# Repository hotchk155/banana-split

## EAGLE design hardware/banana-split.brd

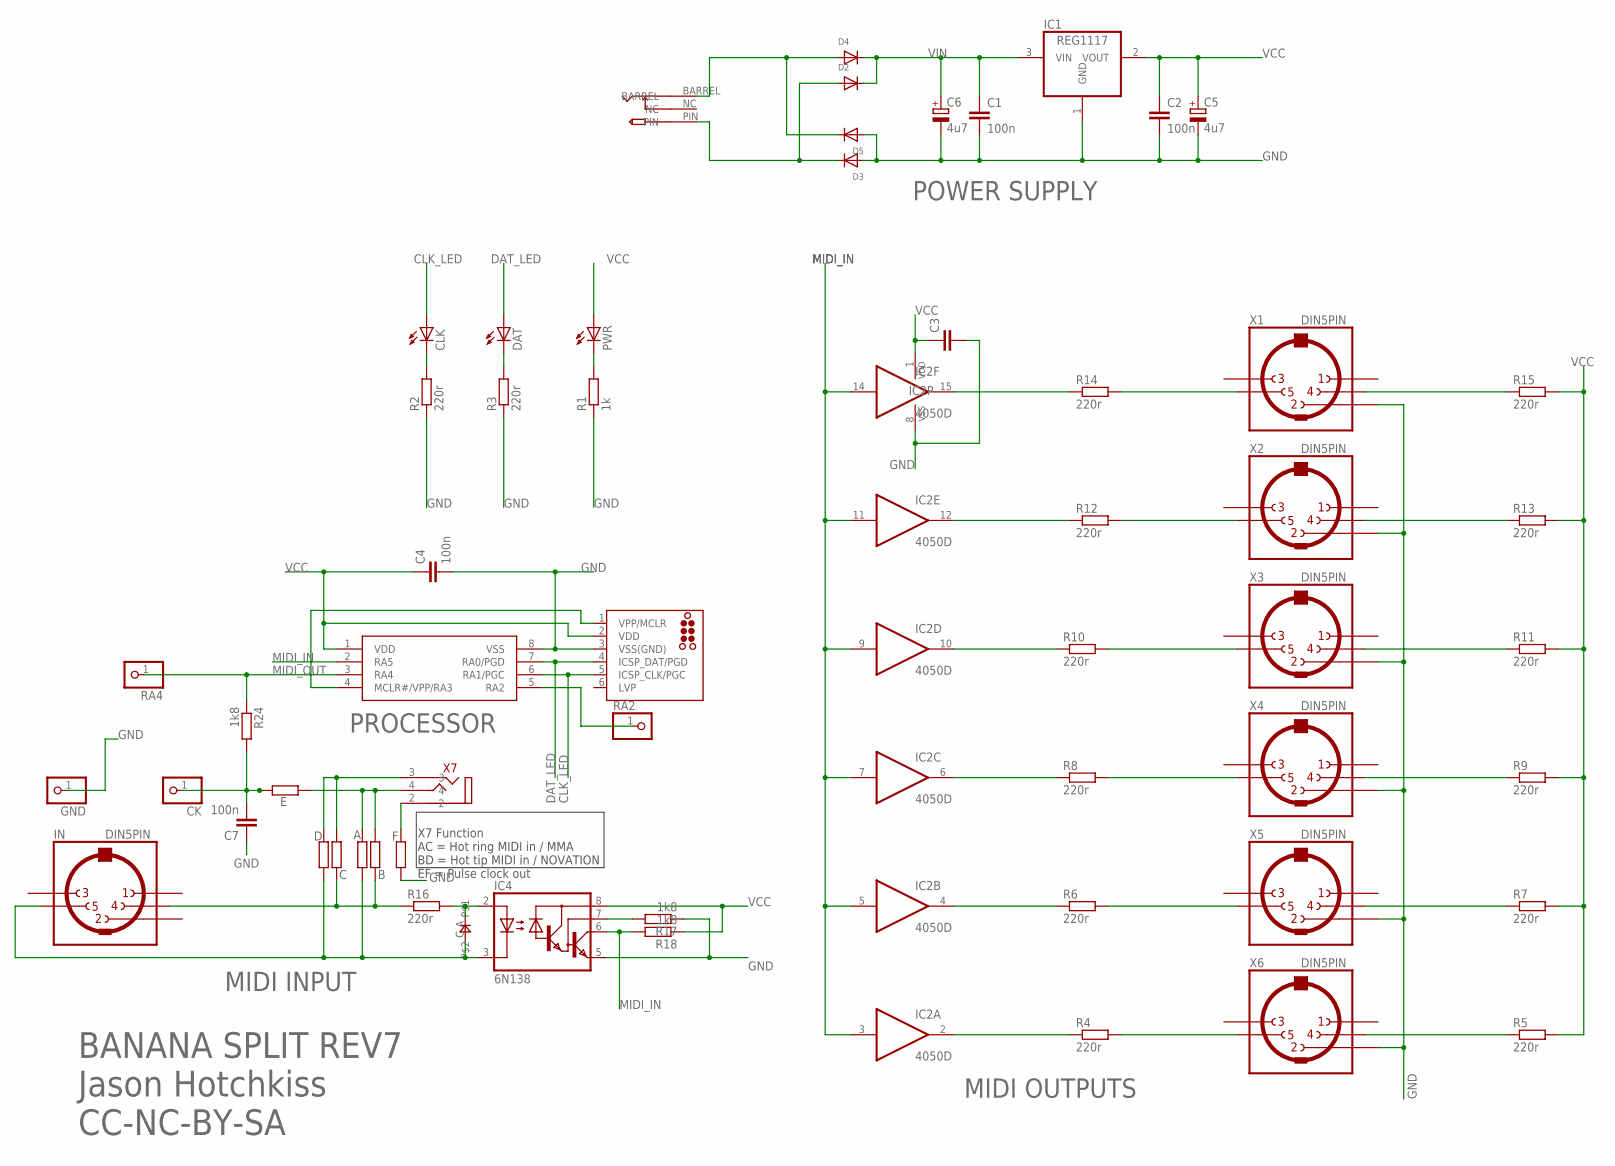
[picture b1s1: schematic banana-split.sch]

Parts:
A: 1k8; R0805
B: 1k8; R0805
C: 1k8; R0805
C1, C2, C4, C7: 100n; C0805
C3: C-EUC0805; C0805
C5, C6: 4u7; E2-4
CK: PINHD-1X1; 1X01
CLK: LED3MM
D: 1k8; R0805
D1: 0805DIODE
D2, D3, D4, D5: DIODESOD-123; SOD-123
DAT: LED3MM
E: 1k8; R0805
F: 1k8; R0805
GND: PINHD-1X1; 1X01
IC1: REG1117; SOT223
IC2: 4050D; SO16
IC3: PIC12F1822SO08; SO08
IC4: 6N138; DIL08
ICSP: TC2030-MCP-NL
IN: DIN5PIN; EDGEDIN
PWR: LED3MM
R1: 1k; R0805
R2, R3, R4, R5, R6, R7, R8, R9, R10, R11, R12, R13, R14, R15, R16: 220r; R0805
R17, R18, R24: 1k8; R0805
RA2, RA4: PINHD-1X1; 1X01
U$1: PWR_SOCKET_2_1MM
X1, X2, X3, X4, X5, X6: DIN5PIN; EDGEDIN
X7: VERTICAL_3_5MM_SOCKET

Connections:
CLK: CLK.K (C), R2.2
CLK_LED: CLK.A, IC3.6 (RA1/PGC), ICSP.5 (ICSP_CLK/PGC)
DAT_LED: DAT.A, IC3.7 (RA0/PGD), ICSP.4 (ICSP_DAT/PGD)
GND: C1.2, C2.2, C3.2, C4.2, C5.-, C6.-, C7.1, D3.A, D5.A, F.1, GND.1, IC1.1 (GND), IC2.8 (VSS), IC3.8 (VSS), IC4.5 (GND), ICSP.3 (VSS(GND)), R1.1, R2.1, R3.1, R17.1, X1.2, X2.2, X3.2, X4.2, X5.2, X6.2
MIDI_IN: IC2.3 (I), IC2.5 (I), IC2.7 (I), IC2.9 (I), IC2.11 (I), IC2.14 (I), IC3.2 (RA5), IC4.6 (VO), R18.2
MIDI_OUT: IC3.3 (RA4), R24.1, RA4.1
unnamed: R14.2, X1.5
unnamed: R12.2, X2.5
unnamed: R10.2, X3.5
unnamed: R8.2, X4.5
unnamed: R6.2, X5.5
unnamed: R4.2, X6.5
unnamed: IC2.15 (O), R14.1
unnamed: IC2.12 (O), R12.1
unnamed: IC2.10 (O), R10.1
unnamed: IC2.6 (O), R8.1
unnamed: IC2.2 (O), R4.1
unnamed: IC2.4 (O), R6.1
unnamed: PWR.K (C), R1.2
unnamed: R15.1, X1.4
unnamed: R13.1, X2.4
unnamed: R11.1, X3.4
unnamed: R9.1, X4.4
unnamed: R7.1, X5.4
unnamed: R5.1, X6.4
unnamed: B.1, C.1, IN.4, R16.1
unnamed: D1.A, IC4.2 (A), R16.2
unnamed: IC4.7 (VB), R17.2
unnamed: DAT.K (C), R3.2
unnamed: A.1, D.1, D1.C, IC4.3 (C), IN.5
unnamed: IC3.5 (RA2), RA2.1
unnamed: C.2, D.2, X7.3
unnamed: D4.A, D5.C, U$1.BARREL
unnamed: D2.A, D3.C, U$1.PIN
unnamed: F.2, X7.2
unnamed: A.2, B.2, E.2, X7.4
unnamed: C7.2, CK.1, E.1, R24.2
unnamed: IC3.4 (MCLR#/VPP/RA3), ICSP.1 (VPP/MCLR)
VCC: C2.1, C3.1, C4.1, C5.+, IC1.2 (VOUT), IC2.1 (VDD), IC3.1 (VDD), IC4.8 (VCC), ICSP.2 (VDD), PWR.A, R5.2, R7.2, R9.2, R11.2, R13.2, R15.2, R18.1
VIN: C1.1, C6.+, D2.C, D4.C, IC1.3 (VIN)

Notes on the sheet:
POWER SUPPLY
MIDI OUTPUTS
MIDI INPUT
PROCESSOR
BANANA SPLIT REV7
Jason Hotchkiss CC-NC-BY-SA
X7 Function AC = Hot ring MIDI in / MMA BD = Hot tip MIDI in / NOVATION EF = Pulse clock out

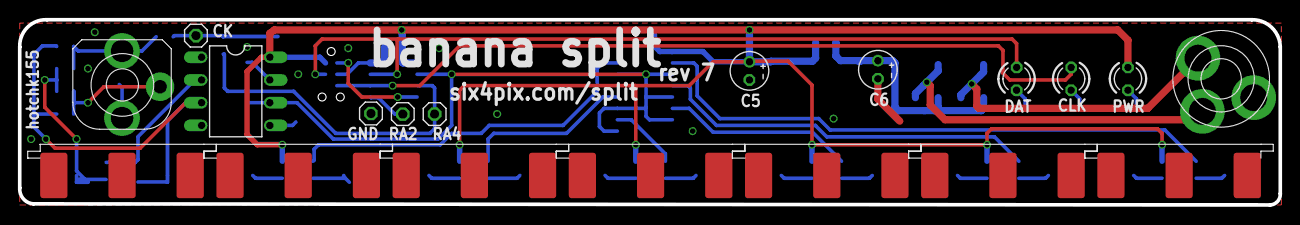
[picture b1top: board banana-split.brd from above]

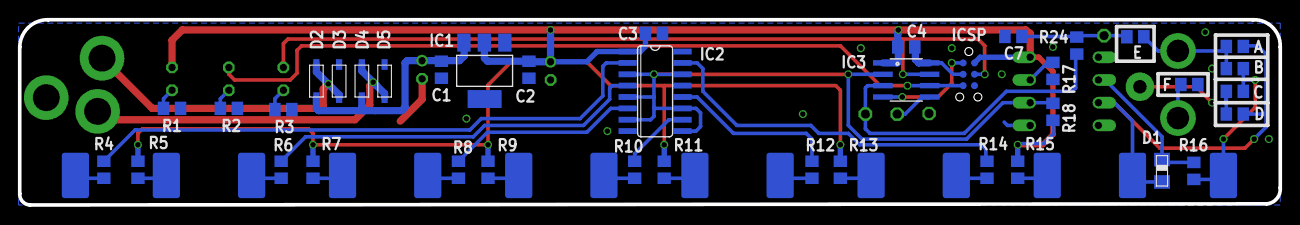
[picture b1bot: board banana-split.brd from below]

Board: 2 copper layers, 140.8 x 20.7 mm, 58 parts (39 on the bottom side), 40 nets.

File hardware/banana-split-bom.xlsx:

Comment | Designator | Footprint | JLCPCB Part #（optional）
0r | A | 0805
DNP | B
0r | C | 0805
100nF | C1 | 0805
100nF | C2 | 0805
100nF | C3 | 0805
100nF | C4 | 0805
100nF | C7 | 0805
DNP | D
TS4148 | D1 | 0805
MBR0520 | D2 | SOD-123
MBR0520 | D3 | SOD-123
MBR0520 | D4 | SOD-123
MBR0520 | D5 | SOD-123
DNP | E
DNP | F
LD1117S50CTR | IC1 | SOT223
CD4050BD | IC2 | SO16
PIC12F1822-I/P | IC3 | SO08
1k | R1 | 0805
220r | R2 | 0805
220r | R3 | 0805
220r | R4 | 0805
220r | R5 | 0805
220r | R6 | 0805
220r | R7 | 0805
220r | R8 | 0805
220r | R9 | 0805
220r | R10 | 0805
220r | R11 | 0805
220r | R12 | 0805
220r | R13 | 0805
220r | R14 | 0805
220r | R15 | 0805
220r | R16 | 0805
1k5 | R17 | 0805
1k5 | R18 | 0805
1k | R24 | 0805

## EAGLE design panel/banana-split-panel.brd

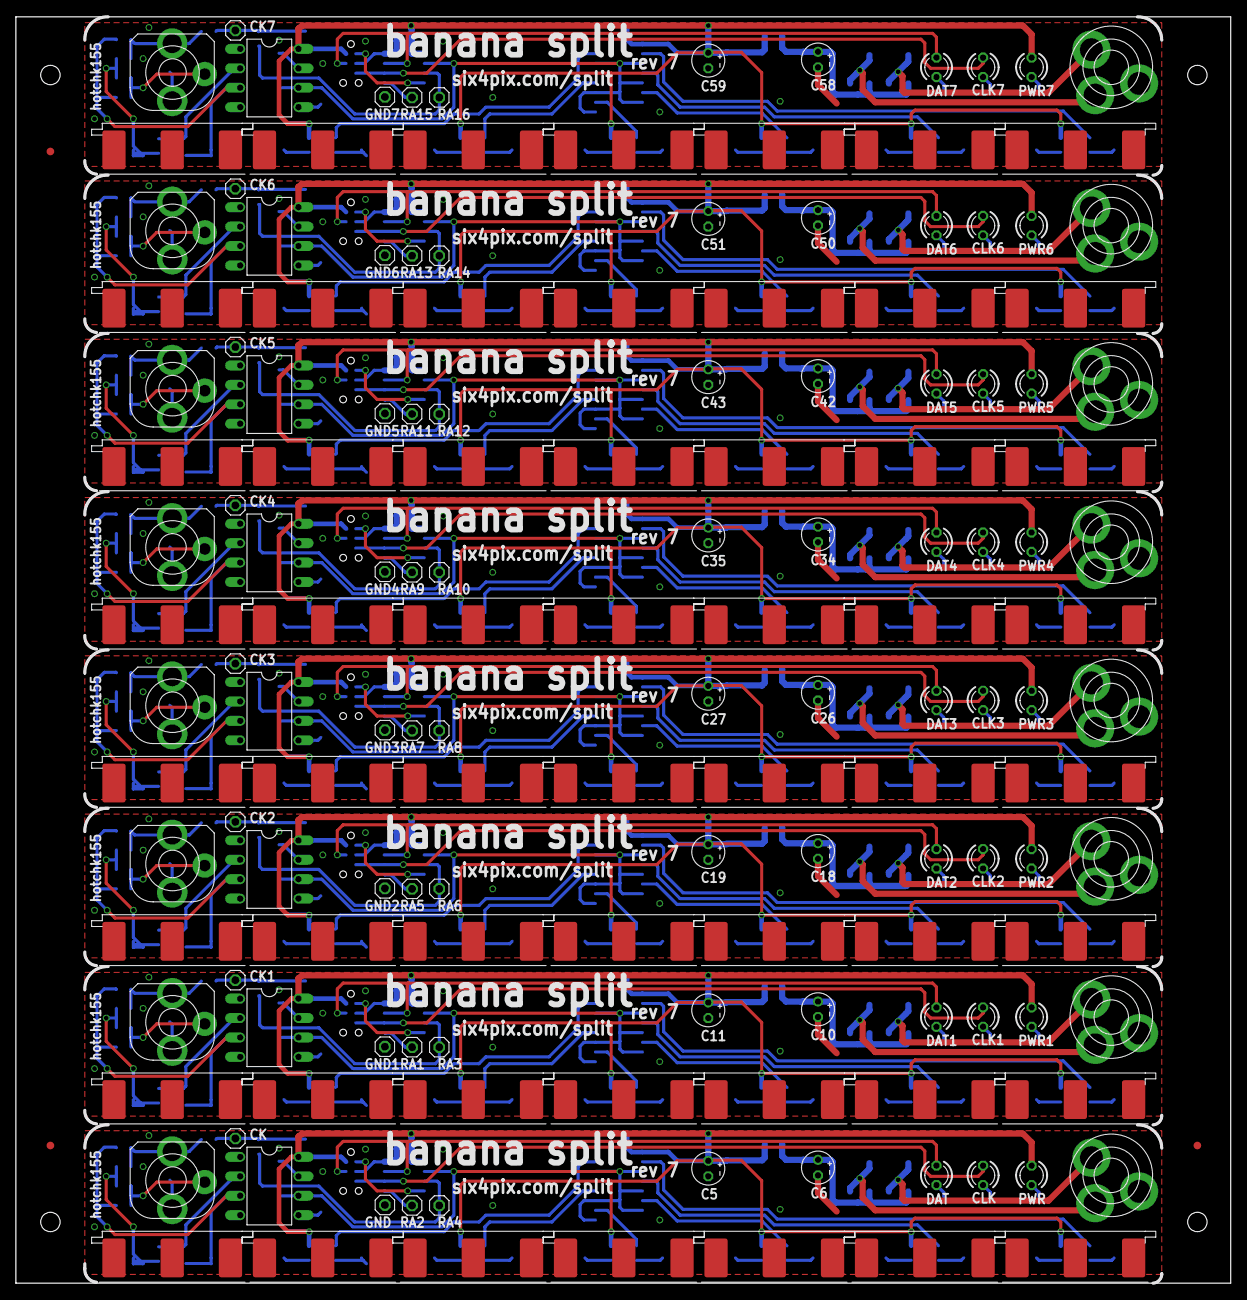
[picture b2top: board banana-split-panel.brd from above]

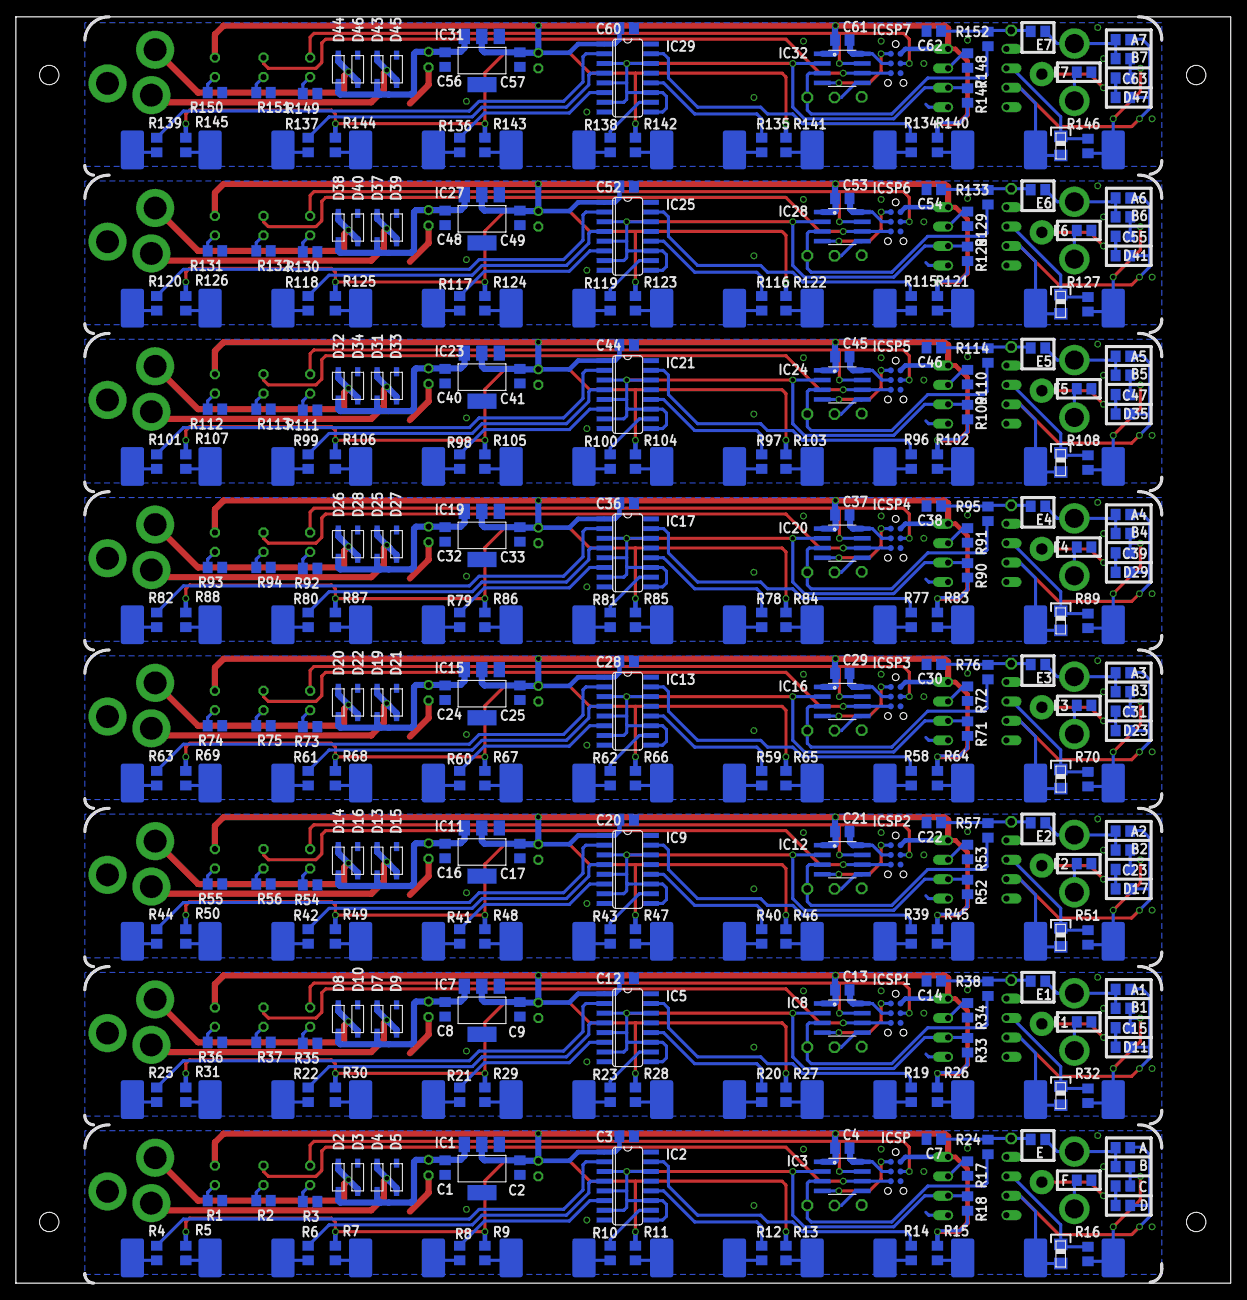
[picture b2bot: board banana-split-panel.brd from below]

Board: 2 copper layers, 158.9 x 165.6 mm, 467 parts (312 on the bottom side), 320 nets.

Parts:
A, A1, A2, A3, A4, A5, A6, A7: 1k8; R0805
B, B1, B2, B3, B4, B5, B6, B7: 1k8; R0805
C, C15, C23, C31, C39, C47, C55, C63: 1k8; R0805
C1, C2, C4, C7, C8, C9, C13, C14, C16, C17, C21, C22, C24, C25, C29, C30, C32, C33, C37, C38, C40, C41, C45, C46, C48, C49, C53, C54, C56, C57, C61, C62: 100n; C0805
C3, C12, C20, C28, C36, C44, C52, C60: C0805
C5, C6, C10, C11, C18, C19, C26, C27, C34, C35, C42, C43, C50, C51, C58, C59: 4u7; E2-4
CK, CK1, CK2, CK3, CK4, CK5, CK6, CK7: 1X01
CLK, CLK1, CLK2, CLK3, CLK4, CLK5, CLK6, CLK7: LED3MM
D, D11, D17, D23, D29, D35, D41, D47: 1k8; R0805
D1, D6, D12, D18, D24, D30, D36, D42: 0805DIODE
D2, D3, D4, D5, D7, D8, D9, D10, D13, D14, D15, D16, D19, D20, D21, D22, D25, D26, D27, D28, D31, D32, D33, D34, D37, D38, D39, D40, D43, D44, D45, D46: SOD-123
DAT, DAT1, DAT2, DAT3, DAT4, DAT5, DAT6, DAT7: LED3MM
E, E1, E2, E3, E4, E5, E6, E7: 1k8; R0805
E$1, E$2, E$3: FIDUCIAL_1MM
F, F1, F2, F3, F4, F5, F6, F7: 1k8; R0805
GND, GND1, GND2, GND3, GND4, GND5, GND6, GND7: 1X01
IC1, IC7, IC11, IC15, IC19, IC23, IC27, IC31: REG1117; SOT223
IC2, IC5, IC9, IC13, IC17, IC21, IC25, IC29: 4050D; SO16
IC3, IC8, IC12, IC16, IC20, IC24, IC28, IC32: PIC12F1822SO08; SO08
IC4, IC6, IC10, IC14, IC18, IC22, IC26, IC30: 6N138; DIL08
ICSP, ICSP1, ICSP2, ICSP3, ICSP4, ICSP5, ICSP6, ICSP7: TC2030-MCP-NL
IN, IN1, IN2, IN3, IN4, IN5, IN6, IN7: DIN5PIN; EDGEDIN
PWR, PWR1, PWR2, PWR3, PWR4, PWR5, PWR6, PWR7: LED3MM
R1, R36, R55, R74, R93, R112, R131, R150: 1k; R0805
R2, R3, R4, R5, R6, R7, R8, R9, R10, R11, R12, R13, R14, R15, R16, R19, R20, R21, R22, R23, R25, R26, R27, R28, R29, R30, R31, R32, R35, R37, R39, R40, R41, R42, R43, R44, R45, R46, R47, R48, R49, R50, R51, R54, R56, R58, R59, R60, R61, R62, R63, R64, R65, R66, R67, R68, R69, R70, R73, R75, R77, R78, R79, R80, R81, R82, R83, R84, R85, R86, R87, R88, R89, R92, R94, R96, R97, R98, R99, R100, R101, R102, R103, R104, R105, R106, R107, R108, R111, R113, R115, R116, R117, R118, R119, R120, R121, R122, R123, R124, R125, R126, R127, R130, R132, R134, R135, R136, R137, R138, R139, R140, R141, R142, R143, R144, R145, R146, R149, R151: 220r; R0805
R17, R18, R24, R33, R34, R38, R52, R53, R57, R71, R72, R76, R90, R91, R95, R109, R110, R114, R128, R129, R133, R147, R148, R152: 1k8; R0805
RA1, RA2, RA3, RA4, RA5, RA6, RA7, RA8, RA9, RA10, RA11, RA12, RA13, RA14, RA15, RA16: 1X01
U$1, U$2, U$3, U$4, U$5, U$6, U$7, U$8: PWR_SOCKET_2_1MM
X1, X2, X3, X4, X5, X6, X8, X9, X10, X11, X12, X13, X15, X16, X17, X18, X19, X20, X22, X23, X24, X25, X26, X27, X29, X30, X31, X32, X33, X34, X36, X37, X38, X39, X40, X41, X43, X44, X45, X46, X47, X48, X50, X51, X52, X53, X54, X55: DIN5PIN; EDGEDIN
X7, X14, X21, X28, X35, X42, X49, X56: VERTICAL_3_5MM_SOCKET

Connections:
CLK: CLK.K, R2.2
CLK1: CLK1.K, R37.2
CLK2: CLK2.K, R56.2
CLK3: CLK3.K, R75.2
CLK4: CLK4.K, R94.2
CLK5: CLK5.K, R113.2
CLK6: CLK6.K, R132.2
CLK7: CLK7.K, R151.2
CLK_LED: CLK.A, IC3.6, ICSP.5
CLK_LED1: CLK1.A, IC8.6, ICSP1.5
CLK_LED2: CLK2.A, IC12.6, ICSP2.5
CLK_LED3: CLK3.A, IC16.6, ICSP3.5
CLK_LED4: CLK4.A, IC20.6, ICSP4.5
CLK_LED5: CLK5.A, IC24.6, ICSP5.5
CLK_LED6: CLK6.A, IC28.6, ICSP6.5
CLK_LED7: CLK7.A, IC32.6, ICSP7.5
DAT_LED: DAT.A, IC3.7, ICSP.4
DAT_LED1: DAT1.A, IC8.7, ICSP1.4
DAT_LED2: DAT2.A, IC12.7, ICSP2.4
DAT_LED3: DAT3.A, IC16.7, ICSP3.4
DAT_LED4: DAT4.A, IC20.7, ICSP4.4
DAT_LED5: DAT5.A, IC24.7, ICSP5.4
DAT_LED6: DAT6.A, IC28.7, ICSP6.4
DAT_LED7: DAT7.A, IC32.7, ICSP7.4
GND: C1.2, C2.2, C3.2, C4.2, C5.-, C6.-, C7.1, D3.A, D5.A, F.1, GND.1, IC1.1, IC2.8, IC3.8, IC4.5, ICSP.3, R1.1, R2.1, R3.1, R17.1, X1.2, X2.2, X3.2, X4.2, X5.2, X6.2
GND1: C8.2, C9.2, C10.-, C11.-, C12.2, C13.2, C14.1, D9.A, D10.A, F1.1, GND1.1, IC5.8, IC6.5, IC7.1, IC8.8, ICSP1.3, R34.1, R35.1, R36.1, R37.1, X8.2, X9.2, X10.2, X11.2, X12.2, X13.2
GND2: C16.2, C17.2, C18.-, C19.-, C20.2, C21.2, C22.1, D15.A, D16.A, F2.1, GND2.1, IC9.8, IC10.5, IC11.1, IC12.8, ICSP2.3, R53.1, R54.1, R55.1, R56.1, X15.2, X16.2, X17.2, X18.2, X19.2, X20.2
GND3: C24.2, C25.2, C26.-, C27.-, C28.2, C29.2, C30.1, D21.A, D22.A, F3.1, GND3.1, IC13.8, IC14.5, IC15.1, IC16.8, ICSP3.3, R72.1, R73.1, R74.1, R75.1, X22.2, X23.2, X24.2, X25.2, X26.2, X27.2
GND4: C32.2, C33.2, C34.-, C35.-, C36.2, C37.2, C38.1, D27.A, D28.A, F4.1, GND4.1, IC17.8, IC18.5, IC19.1, IC20.8, ICSP4.3, R91.1, R92.1, R93.1, R94.1, X29.2, X30.2, X31.2, X32.2, X33.2, X34.2
GND5: C40.2, C41.2, C42.-, C43.-, C44.2, C45.2, C46.1, D33.A, D34.A, F5.1, GND5.1, IC21.8, IC22.5, IC23.1, IC24.8, ICSP5.3, R110.1, R111.1, R112.1, R113.1, X36.2, X37.2, X38.2, X39.2, X40.2, X41.2
GND6: C48.2, C49.2, C50.-, C51.-, C52.2, C53.2, C54.1, D39.A, D40.A, F6.1, GND6.1, IC25.8, IC26.5, IC27.1, IC28.8, ICSP6.3, R129.1, R130.1, R131.1, R132.1, X43.2, X44.2, X45.2, X46.2, X47.2, X48.2
GND7: C56.2, C57.2, C58.-, C59.-, C60.2, C61.2, C62.1, D45.A, D46.A, F7.1, GND7.1, IC29.8, IC30.5, IC31.1, IC32.8, ICSP7.3, R148.1, R149.1, R150.1, R151.1, X50.2, X51.2, X52.2, X53.2, X54.2, X55.2
MIDI_IN: IC2.3, IC2.5, IC2.7, IC2.9, IC2.11, IC2.14, IC3.2, IC4.6, R18.2
MIDI_IN1: IC5.3, IC5.5, IC5.7, IC5.9, IC5.11, IC5.14, IC6.6, IC8.2, R33.2
MIDI_IN2: IC9.3, IC9.5, IC9.7, IC9.9, IC9.11, IC9.14, IC10.6, IC12.2, R52.2
MIDI_IN3: IC13.3, IC13.5, IC13.7, IC13.9, IC13.11, IC13.14, IC14.6, IC16.2, R71.2
MIDI_IN4: IC17.3, IC17.5, IC17.7, IC17.9, IC17.11, IC17.14, IC18.6, IC20.2, R90.2
MIDI_IN5: IC21.3, IC21.5, IC21.7, IC21.9, IC21.11, IC21.14, IC22.6, IC24.2, R109.2
MIDI_IN6: IC25.3, IC25.5, IC25.7, IC25.9, IC25.11, IC25.14, IC26.6, IC28.2, R128.2
MIDI_IN7: IC29.3, IC29.5, IC29.7, IC29.9, IC29.11, IC29.14, IC30.6, IC32.2, R147.2
MIDI_OUT: IC3.3, R24.1, RA4.1
MIDI_OUT1: IC8.3, R38.1, RA3.1
MIDI_OUT2: IC12.3, R57.1, RA6.1
MIDI_OUT3: IC16.3, R76.1, RA8.1
MIDI_OUT4: IC20.3, R95.1, RA10.1
MIDI_OUT5: IC24.3, R114.1, RA12.1
MIDI_OUT6: IC28.3, R133.1, RA14.1
MIDI_OUT7: IC32.3, R152.1, RA16.1
unnamed: R14.2, X1.5
unnamed: R12.2, X2.5
unnamed: R10.2, X3.5
unnamed: R8.2, X4.5
unnamed: R6.2, X5.5
unnamed: R4.2, X6.5
unnamed: IC2.15, R14.1
unnamed: IC2.12, R12.1
unnamed: IC2.10, R10.1
unnamed: IC2.6, R8.1
unnamed: IC2.2, R4.1
unnamed: IC2.4, R6.1
unnamed: PWR.K, R1.2
unnamed: R15.1, X1.4
unnamed: R13.1, X2.4
unnamed: R11.1, X3.4
unnamed: R9.1, X4.4
unnamed: R7.1, X5.4
unnamed: R5.1, X6.4
unnamed: B.1, C.1, IN.4, R16.1
unnamed: D1.A, IC4.2, R16.2
unnamed: IC4.7, R17.2
unnamed: DAT.K, R3.2
unnamed: A.1, D.1, D1.C, IC4.3, IN.5
unnamed: IC3.5, RA2.1
unnamed: C.2, D.2, X7.3
unnamed: D4.A, D5.C, U$1.BARREL
unnamed: D2.A, D3.C, U$1.PIN
unnamed: F.2, X7.2
unnamed: A.2, B.2, E.2, X7.4
unnamed: C7.2, CK.1, E.1, R24.2
unnamed: R19.2, X8.5
unnamed: IC3.4, ICSP.1
unnamed: R20.2, X9.5
unnamed: R23.2, X10.5
unnamed: R21.2, X11.5
unnamed: R22.2, X12.5
unnamed: R25.2, X13.5
unnamed: R26.1, X8.4
unnamed: R27.1, X9.4
unnamed: R28.1, X10.4
unnamed: R29.1, X11.4
unnamed: R30.1, X12.4
unnamed: R31.1, X13.4
unnamed: B1.1, C15.1, IN1.4, R32.1
unnamed: D6.A, IC6.2, R32.2
unnamed: IC6.7, R34.2
unnamed: A1.1, D6.C, D11.1, IC6.3, IN1.5
unnamed: DAT1.K, R35.2
unnamed: D7.A, D9.C, U$2.BARREL
unnamed: D8.A, D10.C, U$2.PIN
unnamed: IC8.4, ICSP1.1
unnamed: PWR1.K, R36.2
unnamed: IC8.5, RA1.1
unnamed: IC5.15, R19.1
unnamed: IC5.12, R20.1
unnamed: IC5.10, R23.1
unnamed: IC5.6, R21.1
unnamed: IC5.2, R25.1
unnamed: IC5.4, R22.1
unnamed: C15.2, D11.2, X14.3
unnamed: A1.2, B1.2, E1.2, X14.4
unnamed: C14.2, CK1.1, E1.1, R38.2
unnamed: F1.2, X14.2
unnamed: R39.2, X15.5
unnamed: R40.2, X16.5
unnamed: R43.2, X17.5
unnamed: R41.2, X18.5
unnamed: R42.2, X19.5
unnamed: R44.2, X20.5
unnamed: R45.1, X15.4
unnamed: R46.1, X16.4
unnamed: R47.1, X17.4
unnamed: R48.1, X18.4
unnamed: R49.1, X19.4
unnamed: R50.1, X20.4
unnamed: B2.1, C23.1, IN2.4, R51.1
unnamed: D12.A, IC10.2, R51.2
unnamed: IC10.7, R53.2
unnamed: A2.1, D12.C, D17.1, IC10.3, IN2.5
unnamed: DAT2.K, R54.2
unnamed: D13.A, D15.C, U$3.BARREL
unnamed: D14.A, D16.C, U$3.PIN
unnamed: IC12.4, ICSP2.1
unnamed: PWR2.K, R55.2
unnamed: IC12.5, RA5.1
unnamed: IC9.15, R39.1
unnamed: IC9.12, R40.1
unnamed: IC9.10, R43.1
unnamed: IC9.6, R41.1
unnamed: IC9.2, R44.1
unnamed: IC9.4, R42.1
unnamed: C23.2, D17.2, X21.3
unnamed: A2.2, B2.2, E2.2, X21.4
unnamed: C22.2, CK2.1, E2.1, R57.2
unnamed: F2.2, X21.2
unnamed: R58.2, X22.5
unnamed: R59.2, X23.5
unnamed: R62.2, X24.5
unnamed: R60.2, X25.5
unnamed: R61.2, X26.5
unnamed: R63.2, X27.5
unnamed: R64.1, X22.4
unnamed: R65.1, X23.4
unnamed: R66.1, X24.4
unnamed: R67.1, X25.4
unnamed: R68.1, X26.4
unnamed: R69.1, X27.4
unnamed: B3.1, C31.1, IN3.4, R70.1
unnamed: D18.A, IC14.2, R70.2
unnamed: IC14.7, R72.2
unnamed: A3.1, D18.C, D23.1, IC14.3, IN3.5
unnamed: DAT3.K, R73.2
unnamed: D19.A, D21.C, U$4.BARREL
unnamed: D20.A, D22.C, U$4.PIN
unnamed: IC16.4, ICSP3.1
unnamed: PWR3.K, R74.2
unnamed: IC16.5, RA7.1
unnamed: IC13.15, R58.1
unnamed: IC13.12, R59.1
unnamed: IC13.10, R62.1
unnamed: IC13.6, R60.1
unnamed: IC13.2, R63.1
unnamed: IC13.4, R61.1
unnamed: C31.2, D23.2, X28.3
unnamed: A3.2, B3.2, E3.2, X28.4
unnamed: C30.2, CK3.1, E3.1, R76.2
unnamed: F3.2, X28.2
unnamed: R77.2, X29.5
unnamed: R78.2, X30.5
unnamed: R81.2, X31.5
unnamed: R79.2, X32.5
unnamed: R80.2, X33.5
unnamed: R82.2, X34.5
unnamed: R83.1, X29.4
unnamed: R84.1, X30.4
unnamed: R85.1, X31.4
unnamed: R86.1, X32.4
unnamed: R87.1, X33.4
unnamed: R88.1, X34.4
unnamed: B4.1, C39.1, IN4.4, R89.1
unnamed: D24.A, IC18.2, R89.2
unnamed: IC18.7, R91.2
unnamed: A4.1, D24.C, D29.1, IC18.3, IN4.5
unnamed: DAT4.K, R92.2
unnamed: D25.A, D27.C, U$5.BARREL
unnamed: D26.A, D28.C, U$5.PIN
unnamed: IC20.4, ICSP4.1
unnamed: PWR4.K, R93.2
unnamed: IC20.5, RA9.1
unnamed: IC17.15, R77.1
unnamed: IC17.12, R78.1
unnamed: IC17.10, R81.1
unnamed: IC17.6, R79.1
unnamed: IC17.2, R82.1
unnamed: IC17.4, R80.1
unnamed: C39.2, D29.2, X35.3
unnamed: A4.2, B4.2, E4.2, X35.4
unnamed: C38.2, CK4.1, E4.1, R95.2
unnamed: F4.2, X35.2
unnamed: R96.2, X36.5
unnamed: R97.2, X37.5
unnamed: R100.2, X38.5
unnamed: R98.2, X39.5
unnamed: R99.2, X40.5
unnamed: R101.2, X41.5
unnamed: R102.1, X36.4
unnamed: R103.1, X37.4
unnamed: R104.1, X38.4
unnamed: R105.1, X39.4
unnamed: R106.1, X40.4
unnamed: R107.1, X41.4
unnamed: B5.1, C47.1, IN5.4, R108.1
unnamed: D30.A, IC22.2, R108.2
unnamed: IC22.7, R110.2
unnamed: A5.1, D30.C, D35.1, IC22.3, IN5.5
unnamed: DAT5.K, R111.2
unnamed: D31.A, D33.C, U$6.BARREL
unnamed: D32.A, D34.C, U$6.PIN
unnamed: IC24.4, ICSP5.1
unnamed: PWR5.K, R112.2
unnamed: IC24.5, RA11.1
unnamed: IC21.15, R96.1
unnamed: IC21.12, R97.1
unnamed: IC21.10, R100.1
unnamed: IC21.6, R98.1
unnamed: IC21.2, R101.1
unnamed: IC21.4, R99.1
unnamed: C47.2, D35.2, X42.3
unnamed: A5.2, B5.2, E5.2, X42.4
unnamed: C46.2, CK5.1, E5.1, R114.2
unnamed: F5.2, X42.2
unnamed: R115.2, X43.5
unnamed: R116.2, X44.5
unnamed: R119.2, X45.5
unnamed: R117.2, X46.5
unnamed: R118.2, X47.5
unnamed: R120.2, X48.5
unnamed: R121.1, X43.4
unnamed: R122.1, X44.4
unnamed: R123.1, X45.4
unnamed: R124.1, X46.4
unnamed: R125.1, X47.4
unnamed: R126.1, X48.4
unnamed: B6.1, C55.1, IN6.4, R127.1
unnamed: D36.A, IC26.2, R127.2
unnamed: IC26.7, R129.2
unnamed: A6.1, D36.C, D41.1, IC26.3, IN6.5
unnamed: DAT6.K, R130.2
unnamed: D37.A, D39.C, U$7.BARREL
unnamed: D38.A, D40.C, U$7.PIN
unnamed: IC28.4, ICSP6.1
unnamed: PWR6.K, R131.2
unnamed: IC28.5, RA13.1
unnamed: IC25.15, R115.1
unnamed: IC25.12, R116.1
unnamed: IC25.10, R119.1
unnamed: IC25.6, R117.1
unnamed: IC25.2, R120.1
unnamed: IC25.4, R118.1
unnamed: C55.2, D41.2, X49.3
unnamed: A6.2, B6.2, E6.2, X49.4
unnamed: C54.2, CK6.1, E6.1, R133.2
unnamed: F6.2, X49.2
unnamed: R134.2, X50.5
unnamed: R135.2, X51.5
unnamed: R138.2, X52.5
unnamed: R136.2, X53.5
unnamed: R137.2, X54.5
unnamed: R139.2, X55.5
unnamed: R140.1, X50.4
unnamed: R141.1, X51.4
unnamed: R142.1, X52.4
unnamed: R143.1, X53.4
unnamed: R144.1, X54.4
unnamed: R145.1, X55.4
unnamed: B7.1, C63.1, IN7.4, R146.1
unnamed: D42.A, IC30.2, R146.2
unnamed: IC30.7, R148.2
unnamed: A7.1, D42.C, D47.1, IC30.3, IN7.5
unnamed: DAT7.K, R149.2
unnamed: D43.A, D45.C, U$8.BARREL
unnamed: D44.A, D46.C, U$8.PIN
unnamed: IC32.4, ICSP7.1
unnamed: PWR7.K, R150.2
unnamed: IC32.5, RA15.1
unnamed: IC29.15, R134.1
unnamed: IC29.12, R135.1
unnamed: IC29.10, R138.1
unnamed: IC29.6, R136.1
unnamed: IC29.2, R139.1
unnamed: IC29.4, R137.1
unnamed: C63.2, D47.2, X56.3
unnamed: A7.2, B7.2, E7.2, X56.4
unnamed: C62.2, CK7.1, E7.1, R152.2
unnamed: F7.2, X56.2
VCC: C2.1, C3.1, C4.1, C5.+, IC1.2, IC2.1, IC3.1, IC4.8, ICSP.2, PWR.A, R5.2, R7.2, R9.2, R11.2, R13.2, R15.2, R18.1
VCC1: C9.1, C11.+, C12.1, C13.1, IC5.1, IC6.8, IC7.2, IC8.1, ICSP1.2, PWR1.A, R26.2, R27.2, R28.2, R29.2, R30.2, R31.2, R33.1
VCC2: C17.1, C19.+, C20.1, C21.1, IC9.1, IC10.8, IC11.2, IC12.1, ICSP2.2, PWR2.A, R45.2, R46.2, R47.2, R48.2, R49.2, R50.2, R52.1
VCC3: C25.1, C27.+, C28.1, C29.1, IC13.1, IC14.8, IC15.2, IC16.1, ICSP3.2, PWR3.A, R64.2, R65.2, R66.2, R67.2, R68.2, R69.2, R71.1
VCC4: C33.1, C35.+, C36.1, C37.1, IC17.1, IC18.8, IC19.2, IC20.1, ICSP4.2, PWR4.A, R83.2, R84.2, R85.2, R86.2, R87.2, R88.2, R90.1
VCC5: C41.1, C43.+, C44.1, C45.1, IC21.1, IC22.8, IC23.2, IC24.1, ICSP5.2, PWR5.A, R102.2, R103.2, R104.2, R105.2, R106.2, R107.2, R109.1
VCC6: C49.1, C51.+, C52.1, C53.1, IC25.1, IC26.8, IC27.2, IC28.1, ICSP6.2, PWR6.A, R121.2, R122.2, R123.2, R124.2, R125.2, R126.2, R128.1
VCC7: C57.1, C59.+, C60.1, C61.1, IC29.1, IC30.8, IC31.2, IC32.1, ICSP7.2, PWR7.A, R140.2, R141.2, R142.2, R143.2, R144.2, R145.2, R147.1
VIN: C1.1, C6.+, D2.C, D4.C, IC1.3
VIN1: C8.1, C10.+, D7.C, D8.C, IC7.3
VIN2: C16.1, C18.+, D13.C, D14.C, IC11.3
VIN3: C24.1, C26.+, D19.C, D20.C, IC15.3
VIN4: C32.1, C34.+, D25.C, D26.C, IC19.3
VIN5: C40.1, C42.+, D31.C, D32.C, IC23.3
VIN6: C48.1, C50.+, D37.C, D38.C, IC27.3
VIN7: C56.1, C58.+, D43.C, D44.C, IC31.3

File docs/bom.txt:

Partlist exported from D:/GitHub/banana-split/hardware/banana-split.sch at 16/09/2017 11:13:05

Part Value                 Device                Package               Description                                         MF                MPN     OC_FARNELL OC_NEWARK
C1   100n                  C-EUC0805             C0805                 CAPACITOR, European symbol                                                                        
C2   100n                  C-EUC0805             C0805                 CAPACITOR, European symbol                                                                        
C3                         C-EUC0805             C0805                 CAPACITOR, European symbol                                                                        
C4   100n                  C-EUC0805             C0805                 CAPACITOR, European symbol                                                                        
C5   4u7                   CPOL-EUE2-4           E2-4                  POLARIZED CAPACITOR, European symbol                                                              
C6   4u7                   CPOL-EUE2-4           E2-4                  POLARIZED CAPACITOR, European symbol                                                              
CLK                        LED3MM                LED3MM                LED                                                                                               
D1   0805DIODE             0805DIODE             0805DIODE                                                                                                               
DAT                        LED3MM                LED3MM                LED                                                                                               
IC1  REG1117               REG1117               SOT223                800mA and 1A Low Dropout (LDO) Positive Regulator                     REG1117 1097566    14P6981  
IC2  4050D                 4050D                 SO16                  Hex non-inverting BUFFER                                                                          
IC3  PIC12F1822SO08        PIC12F1822SO08        SO08                                                                                                                    
IC4  6N138                 6N138                 DIL08                 MOTOROLA OPTO COUPLER                               VISHAY/TELEFUNKEN 6N138   9860150    35K5294  
IC5                        BRIDGERECTIFIER       SOIC-4                Bridge Rectifier                                                                                  
ICSP                       TC2030-MCP-NL         TC2030-MCP-NL         TAG-CONNECT ICSP ConnectorManufacturer: Tag-Connect                                               
IN   DIN5PIN               DIN5PIN               EDGEDIN               Female CONNECTOR                                                                                  
PWR                        LED3MM                LED3MM                LED                                                                                               
R1   1k                    R-EU_R0805            R0805                 RESISTOR, European symbol                                                                         
R2   220r                  R-EU_R0805            R0805                 RESISTOR, European symbol                                                                         
R3   220r                  R-EU_R0805            R0805                 RESISTOR, European symbol                                                                         
R4   220r                  R-EU_R0805            R0805                 RESISTOR, European symbol                                                                         
R5   220r                  R-EU_R0805            R0805                 RESISTOR, European symbol                                                                         
R6   220r                  R-EU_R0805            R0805                 RESISTOR, European symbol                                                                         
R7   220r                  R-EU_R0805            R0805                 RESISTOR, European symbol                                                                         
R8   220r                  R-EU_R0805            R0805                 RESISTOR, European symbol                                                                         
R9   220r                  R-EU_R0805            R0805                 RESISTOR, European symbol                                                                         
R10  220r                  R-EU_R0805            R0805                 RESISTOR, European symbol                                                                         
R11  220r                  R-EU_R0805            R0805                 RESISTOR, European symbol                                                                         
R12  220r                  R-EU_R0805            R0805                 RESISTOR, European symbol                                                                         
R13  220r                  R-EU_R0805            R0805                 RESISTOR, European symbol                                                                         
R14  220r                  R-EU_R0805            R0805                 RESISTOR, European symbol                                                                         
R15  220r                  R-EU_R0805            R0805                 RESISTOR, European symbol                                                                         
R16  220r                  R-EU_R0805            R0805                 RESISTOR, European symbol                                                                         
R17  1k8                   R-EU_R0805            R0805                 RESISTOR, European symbol                                                                         
R18  1k8                   R-EU_R0805            R0805                 RESISTOR, European symbol                                                                         
RA2                        PINHD-1X1             1X01                  PIN HEADER                                                                                        
RA4                        PINHD-1X1             1X01                  PIN HEADER                                                                                        
U$1  PWR_SOCKET_2_1MM      PWR_SOCKET_2_1MM      PWR_SOCKET_2_1MM                                                                                                        
X1   DIN5PIN               DIN5PIN               EDGEDIN               Female CONNECTOR                                                                                  
X2   DIN5PIN               DIN5PIN               EDGEDIN               Female CONNECTOR                                                                                  
X3   DIN5PIN               DIN5PIN               EDGEDIN               Female CONNECTOR                                                                                  
X4   DIN5PIN               DIN5PIN               EDGEDIN               Female CONNECTOR                                                                                  
X5   DIN5PIN               DIN5PIN               EDGEDIN               Female CONNECTOR                                                                                  
X6   DIN5PIN               DIN5PIN               EDGEDIN               Female CONNECTOR                                                                                  
X7   VERTICAL_3_5MM_SOCKET VERTICAL_3_5MM_SOCKET VERTICAL_3_5MM_SOCKET

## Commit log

2015-10-12 :lollipop: Added .gitattributes & .gitignore files
2015-10-12 pcb ready
2015-11-10 gitignore
2016-01-30 add component values
2016-06-14 REV3 PCB
2016-08-16 version 1 release
2016-11-25 V4 - Grounding output GND pins!
2016-11-25 cleanup
2016-11-30 rename
2018-04-30 checkin stuff
2018-05-09 Version 2 firmware - sixteenth pulse clock
2018-06-01 Version 3 release candidate
2019-05-28 mod doc
2019-07-11 V5 PCB
2019-08-19 v6 candidate
2019-09-06 V7 PCB
2019-09-07 V7 - layers tweak
2019-09-07 v7 panel
2019-09-08 v7 prod?
2019-10-11 input options v7
2019-10-16 changes for v7
2020-06-03 eqew
2020-06-03 fix issue with ground pour on panel
2021-03-26 gerbers
2021-07-31 test to run on adapted orange squeeze hardware
2025-12-12 PCBA setup

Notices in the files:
parts and their libraries:
tag-connect: ©2009 ROFA.cz - modified and updated by Robert Darlington ‹rdarlington@gmail.com›
